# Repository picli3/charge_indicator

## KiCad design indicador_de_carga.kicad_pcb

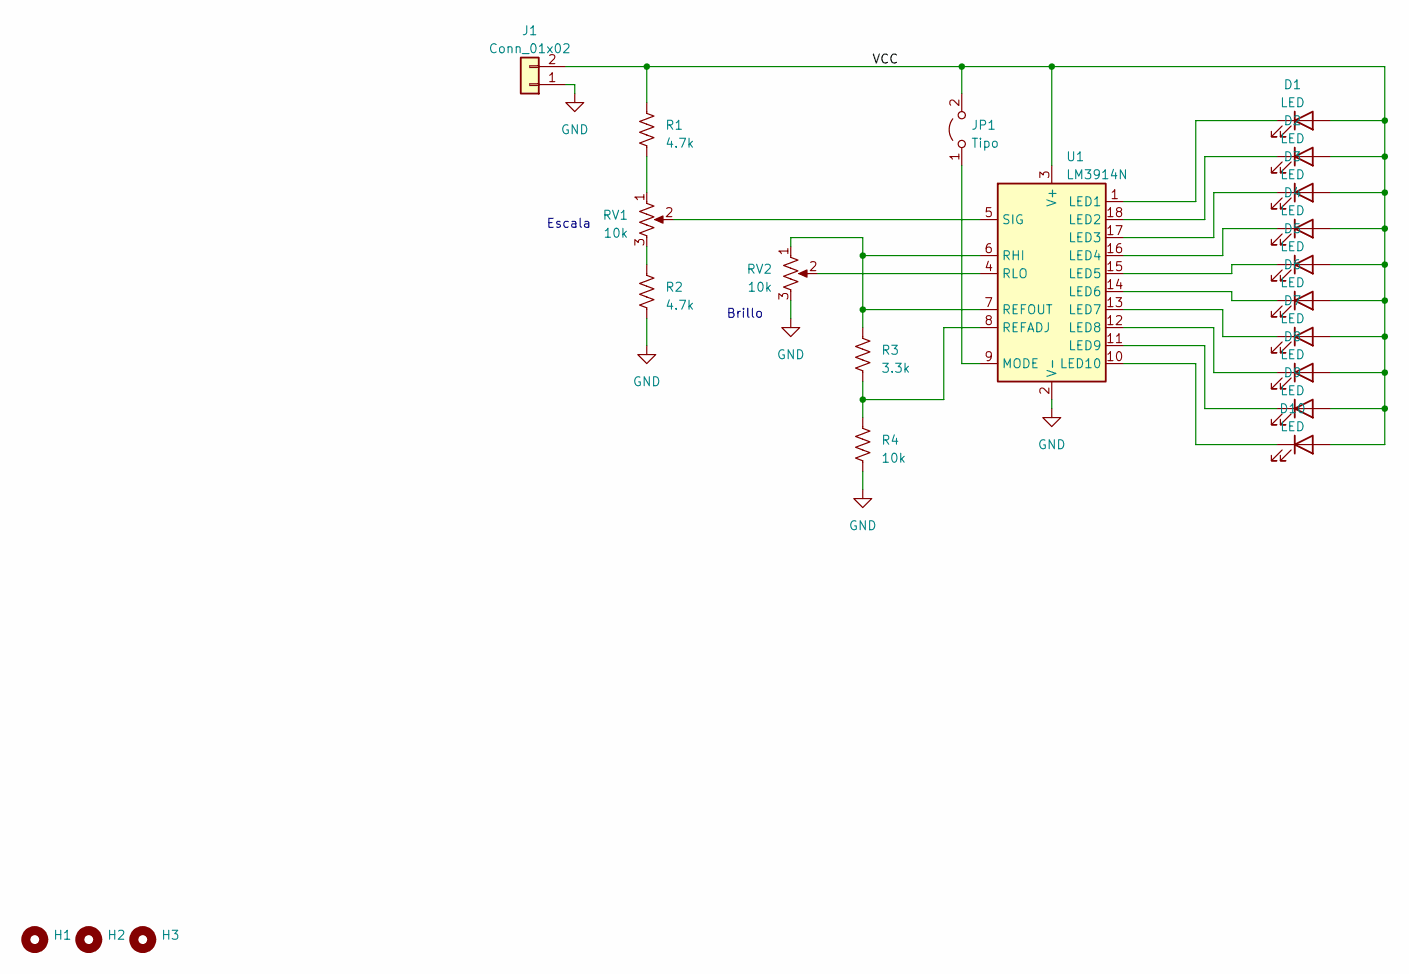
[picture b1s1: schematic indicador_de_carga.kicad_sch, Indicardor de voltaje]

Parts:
D1, D2, D3, D4, D5, D6, D7, D8, D9, D10: LED; LED_D3.0mm
H1, H2, H3: MountingHole; MountingHole_3.2mm_M3_DIN965_Pad
J1: Conn_01x02; TerminalBlock_Phoenix_MKDS-1,5-2-5.08_1x02_P5.08mm_Horizont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
JP1: Tipo; SolderJumper-2_P1.3mm_Open_TrianglePad1.0x1.5mm
R1, R2: 4.7k; R_Axial_DIN0207_L6.3mm_D2.5mm_P10.16mm_Horizontal
R3: 3.3k; R_Axial_DIN0207_L6.3mm_D2.5mm_P10.16mm_Horizontal
R4: 10k; R_Axial_DIN0207_L6.3mm_D2.5mm_P10.16mm_Horizontal
RV1, RV2: 10k; Potentiometer_Runtron_RM-065_Vertical
U1: LM3914N; DIP-18_W7.62mm

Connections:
/VCC: D1.2 (A), D2.2 (A), D3.2 (A), D4.2 (A), D5.2 (A), D6.2 (A), D7.2 (A), D8.2 (A), D9.2 (A), D10.2 (A), J1.2, JP1.2 (B), R1.1, U1.3 (V+)
GND: J1.1, R2.2, R4.2, RV2.3, U1.2 (V-)
unnamed: D1.1 (K), U1.1 (LED1)
unnamed: D2.1 (K), U1.18 (LED2)
unnamed: D3.1 (K), U1.17 (LED3)
unnamed: D4.1 (K), U1.16 (LED4)
unnamed: D5.1 (K), U1.15 (LED5)
unnamed: D6.1 (K), U1.14 (LED6)
unnamed: D7.1 (K), U1.13 (LED7)
unnamed: D8.1 (K), U1.12 (LED8)
unnamed: D9.1 (K), U1.11 (LED9)
unnamed: D10.1 (K), U1.10 (LED10)
unnamed: JP1.1 (A), U1.9 (MODE)
unnamed: R1.2, RV1.1
unnamed: R2.1, RV1.3
unnamed: R3.2, R4.1, U1.8 (REFADJ)
unnamed: R3.1, RV2.1, U1.6 (RHI), U1.7 (REFOUT)
unnamed: RV2.2, U1.4 (RLO)
unnamed: RV1.2, U1.5 (SIG)

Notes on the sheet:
Escala
Brillo

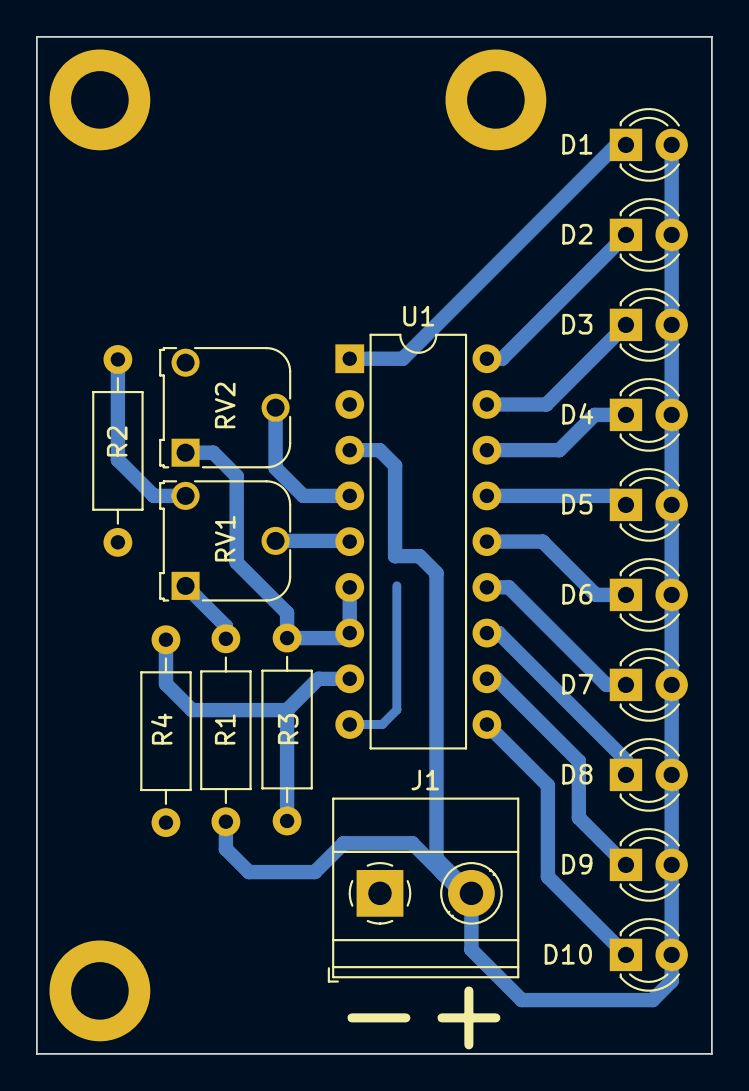
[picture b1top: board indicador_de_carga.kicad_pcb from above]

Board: 2 copper layers, 37.5 x 56.5 mm, 22 parts (1 on the bottom side), 19 nets.

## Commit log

2023-12-08 proyecto terminado
